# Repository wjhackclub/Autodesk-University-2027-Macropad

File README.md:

# Macropad

A wireless BLE keyboard the size of your hand.

This project was made for Autodesk University 2027 to assist apps without autocomplete. The Macropad uses the ESP32 core chip for latency-free Bluetooth transmission, taking sub 50ms. Features include key debouncing, a status LED indicator, a quick swap keybind changing tool, and an internal memory storage bank. Menu choices and key layouts can be configured easily using the desktop app. When a key is pressed either word, sentence, or code the phrase from your computer is sent over wifi to a local 3.5b parameter AI on the Arduino Uno Q where it is processed and sent back as a complete phrase.

## BOM

| Component | Description | Quantity | Approx Price (USD) |
| :--- | :--- | :--- | :--- |
| **ESP32 Dev Kit** | Microcontroller | 1 | $4.50 |
| **Tactile Buttons** | Tap input keys (any brand cherry mx style) | 3 | $0.30 |
| **Status LED** | Indication led for network states | 1 | $0.10 |
| **FR1 Copper Clad Sheet** | Base board for pcb | 1 | $1.00 |
| **Total Cost** | -- | -- | **~$5.90** |

---

## How it works

### 1. Keyboard Firmware
The ESP32 mimics a standard Bluetooth keyboard so your computer recognizes and trusts it. At the same time, it leaves a connection open for your Windows application to connect. This lets you rebind your gaming keys instantly without losing connection. Once sent, the new keys save directly to the onboard memory so they stick even after a reboot.

### 2. Desktop Firmware
Windows recognizes the Macropad as a standard USB device when it is plugged in. The desktop app connects directly to this active USB port and listens for the hardware footprint. Once selected, it streams your new keybind configuration data through the cable.

---
## Wiring Guide

```text
Button Wiring:
* Button 1       | GPIO 0 | GND
* Button 2       | GPIO 1 | GND
* Button 3       | GPIO 2 | GND

Battery Wiring:
* Battery (+)    | TP4056 (B+)
* Battery (-)    | TP4056 (B-)
* TP4056 (OUT-)  | ESP32 (GND)
* TP4056 (OUT+)  | Switch (Middle Pin)
* Switch (Outer) | ESP32 (VIN / 5V)

LED Wiring:
* Long Leg (+)   | ESP32 (GPIO 4)
* Short Leg (-)  | ESP32 (GND)
```

## Building & Compiling

### Arduino Firmware Setup
Ensure you have the `NimBLE-Arduino` package installed through your library manager. Compile and flash the script directly to your ESP32 board.

### Native Windows App Compilation
If you make modifications to the Python app script, re-bundle the project into an `.exe` using the system tool command:

```powershell
# Setup requirements
pip install bleak customtkinter pyinstaller

# Build into a executable
python -m PyInstaller --noconsole --onefile keybinds.py
```
Your compiled launcher will be placed cleanly inside the newly generated `/dist` directory.

Currently WIP when the Uno Q arrives I will begin coding the AI functions.

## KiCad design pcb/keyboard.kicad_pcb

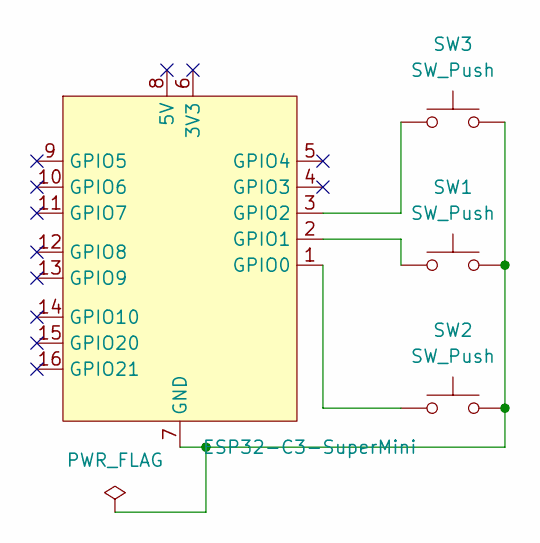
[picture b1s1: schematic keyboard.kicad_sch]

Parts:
SW1, SW2, SW3: SW_Push; MX-Solderable-1U
U1: ESP32-C3-SuperMini

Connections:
unnamed: SW1.2, SW2.2, SW3.2, U1.7 (GND)
unnamed: SW2.1, U1.1 (GPIO0)
unnamed: SW1.1, U1.2 (GPIO1)
unnamed: SW3.1, U1.3 (GPIO2)

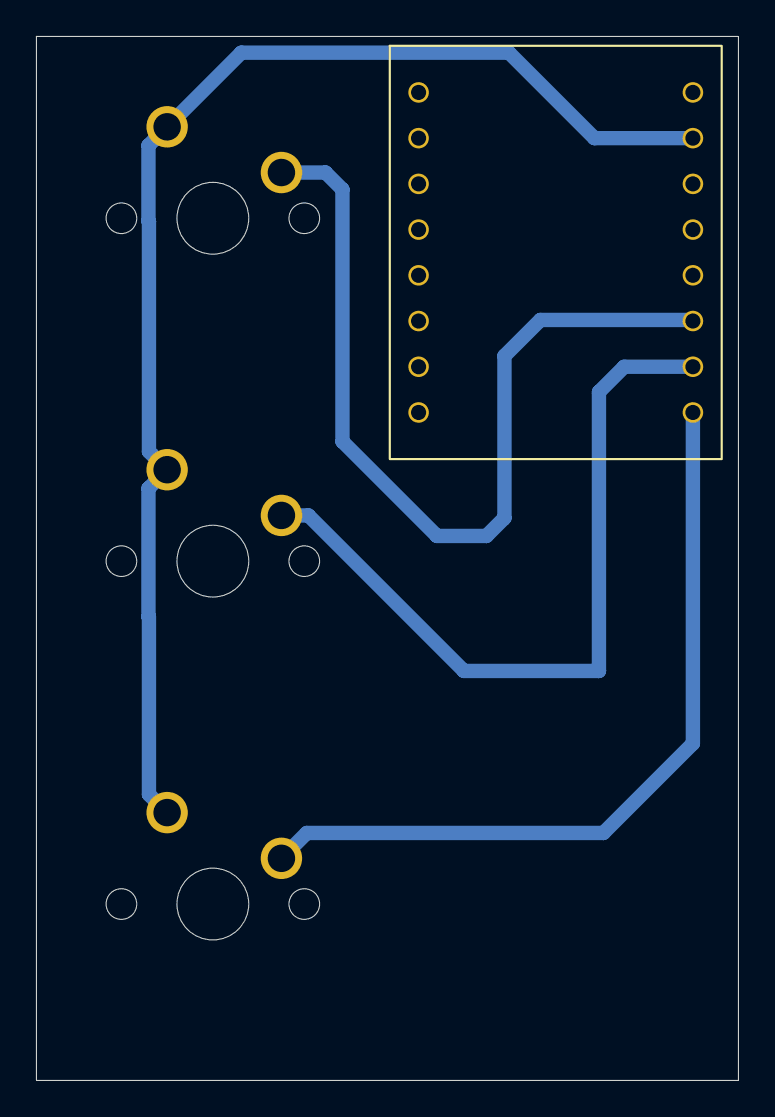
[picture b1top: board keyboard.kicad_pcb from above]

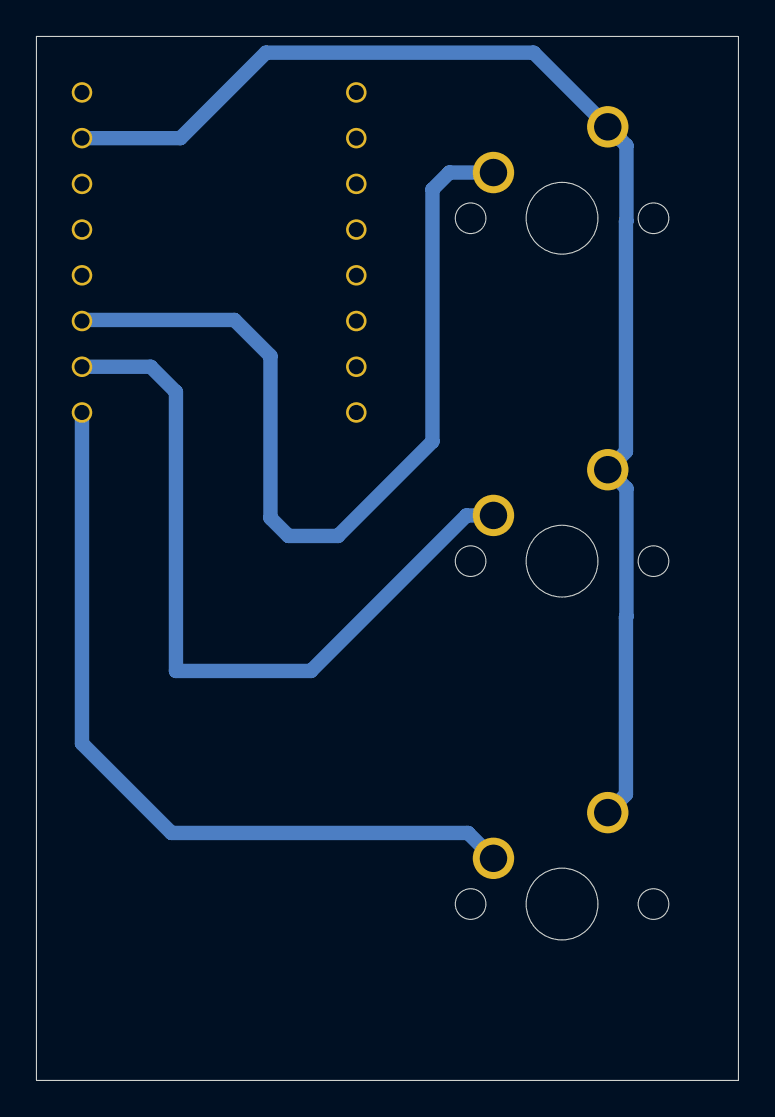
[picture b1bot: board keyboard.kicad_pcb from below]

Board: 2 copper layers, 39.0 x 58.0 mm, 4 parts (3 on the bottom side), 4 nets.
